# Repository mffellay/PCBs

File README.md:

# PCBs
Personal PCB projects (KiCAD)

**Guitar pedal power supply with 6 isolated outputs**

**USB Audio Interface**
*Ongoing*

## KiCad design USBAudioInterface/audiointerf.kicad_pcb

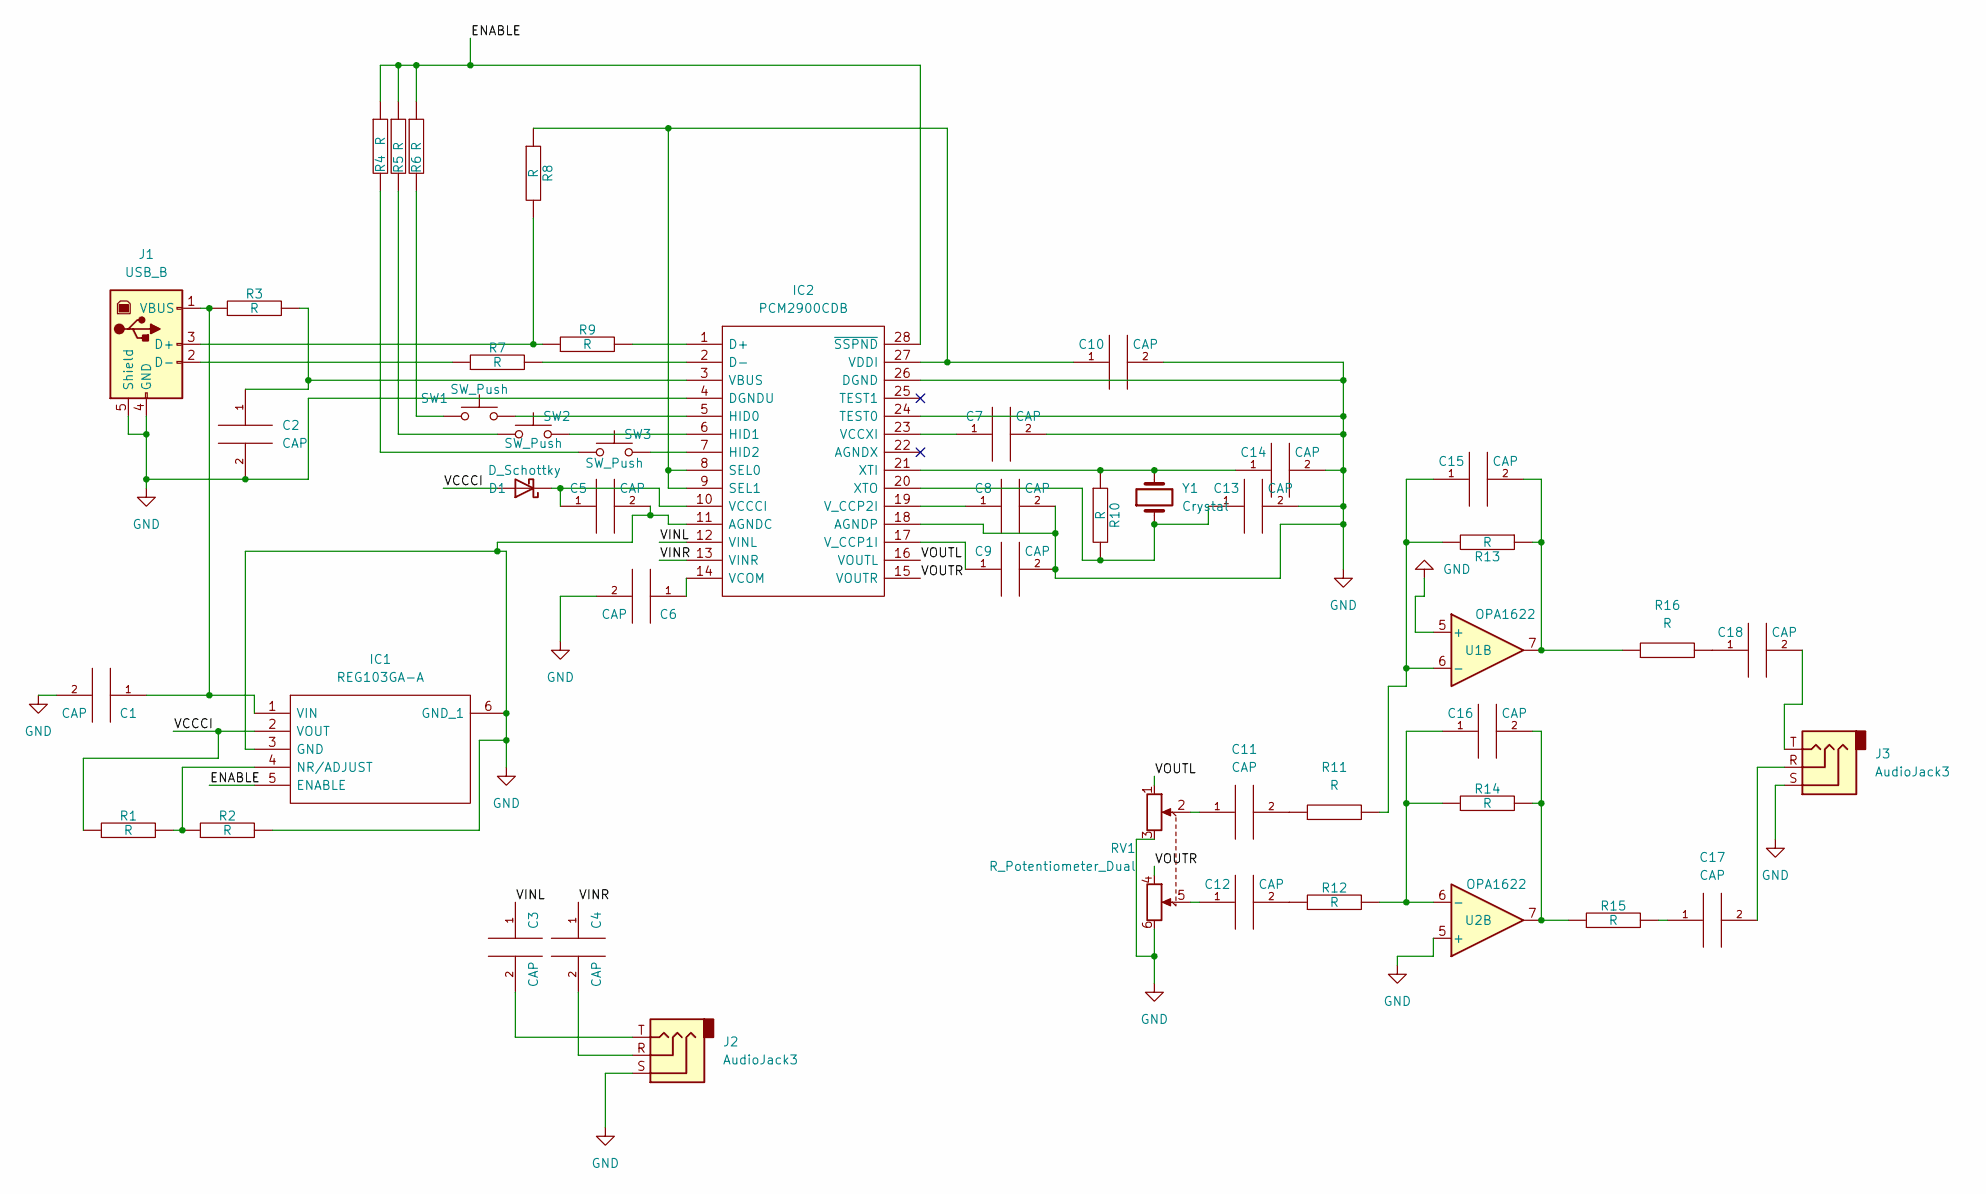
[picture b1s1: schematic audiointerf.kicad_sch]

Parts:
C1, C2, C7, C8, C9, C10, C13, C14, C15, C16, C17, C18: CAP; CP_EIA-2012-15_AVX-P
C3, C4, C5, C6, C11, C12: CAP; CP_Radial_D5.0mm_P2.50mm
D1: D_Schottky; D_2114_3652Metric
IC1: REG103GA-A; SOT-223-6; Manufacturer_Part_Number REG103GA-A; Mouser Part Number 595-REG103GA-A
IC2: PCM2900CDB; SSOP-28_5.3x10.2mm_P0.65mm; Manufacturer_Part_Number PCM2900CDB; Mouser Part Number 595-PCM2900CDB
J1: USB_B; USB_B_Lumberg_2411_02_Horizontal
J2: AudioJack3; Jack_6.35mm_Neutrik_NJ3FD-V_Vertical
J3: AudioJack3; Jack_3.5mm_CUI_SJ-3523-SMT_Horizontal
R1, R2, R3, R4, R5, R6, R7, R8, R9, R10, R11, R12, R13, R14, R15, R16: R; R_0603_1608Metric
RV1: R_Potentiometer_Dual; Potentiometer_Alpha_RD902F-40-00D_Dual_Vertical
SW1, SW2, SW3: SW_Push; SW_CW_GPTS203211B
U1, U2: OPA1622; Texas_S-PVSON-N10
Y1: Crystal; Crystal_DS10_D1.0mm_L4.3mm_Horizontal

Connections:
/ENABLE: IC1.5 (ENABLE), IC2.28 (~SSPND), R4.1, R5.1, R6.1
/VCCCI: D1.2 (A), IC1.2 (VOUT), R1.1
/VINL: C3.1, IC2.12 (VINL)
/VINR: C4.1, IC2.13 (VINR)
/VOUTL: IC2.16 (VOUTL), RV1.1
/VOUTR: IC2.15 (VOUTR), RV1.4
GND: C1.2, C2.2, C5.2, C6.2, C7.2, C8.2, C9.2, C10.2, C13.2, C14.2, IC1.3 (GND), IC1.6 (GND_1), IC2.4 (DGNDU), IC2.11 (AGNDC), IC2.18 (AGNDP), IC2.24 (TEST0), IC2.26 (DGND), J1.4 (GND), J1.5 (Shield), J2.S, J3.S, R2.2, RV1.3, RV1.6, U1.5 (+), U2.5 (+)
unnamed: C1.1, IC1.1 (VIN), J1.1 (VBUS), R3.1
unnamed: C2.1, IC2.3 (VBUS), R3.2
unnamed: C3.2, J2.T
unnamed: C4.2, J2.R
unnamed: C5.1, D1.1 (K), IC2.10 (VCCCI)
unnamed: C6.1, IC2.14 (VCOM)
unnamed: C7.1, IC2.23 (VCCXI)
unnamed: C8.1, IC2.19 (V_CCP2I)
unnamed: C9.1, IC2.17 (V_CCP1I)
unnamed: C10.1, IC2.8 (SEL0), IC2.9 (SEL1), IC2.27 (VDDI), R8.1
unnamed: C11.1, RV1.2
unnamed: C11.2, R11.1
unnamed: C12.1, RV1.5
unnamed: C12.2, R12.1
unnamed: C13.1, IC2.20 (XTO), R10.2, Y1.1
unnamed: C14.1, IC2.21 (XTI), R10.1, Y1.2
unnamed: C16.1, R12.2, R14.1, U2.6 (-)
unnamed: C16.2, R14.2, R15.1, U2.7
unnamed: C17.1, R15.2
unnamed: C17.2, J3.R
unnamed: C18.1, R16.2
unnamed: C18.2, J3.T
unnamed: IC1.4 (NR/ADJUST), R1.2, R2.1
unnamed: IC2.1 (D+), R9.2
unnamed: IC2.2 (D-), R7.2
unnamed: IC2.5 (HID0), SW1.2
unnamed: IC2.6 (HID1), SW2.2
unnamed: IC2.7 (HID2), SW3.2
unnamed: J1.2 (D-), R7.1
unnamed: J1.3 (D+), R8.2, R9.1
unnamed: R4.2, SW3.1
unnamed: R5.2, SW2.1
unnamed: R6.2, SW1.1

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
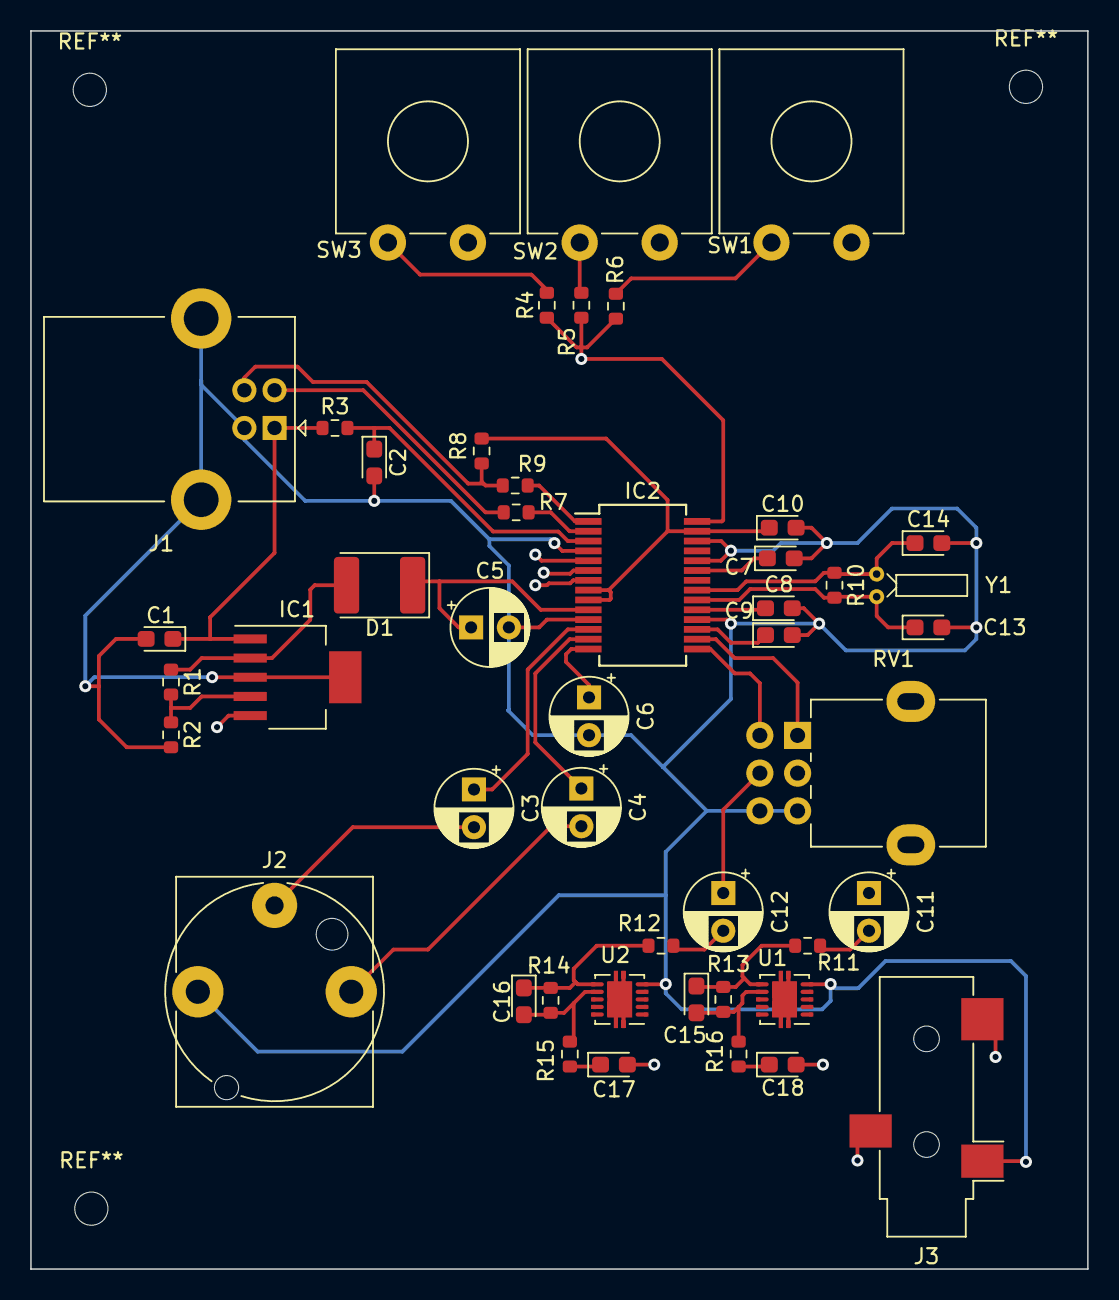
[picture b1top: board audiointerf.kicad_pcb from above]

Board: 4 copper layers, 70.0 x 82.0 mm, 47 parts (0 on the bottom side), 42 nets.

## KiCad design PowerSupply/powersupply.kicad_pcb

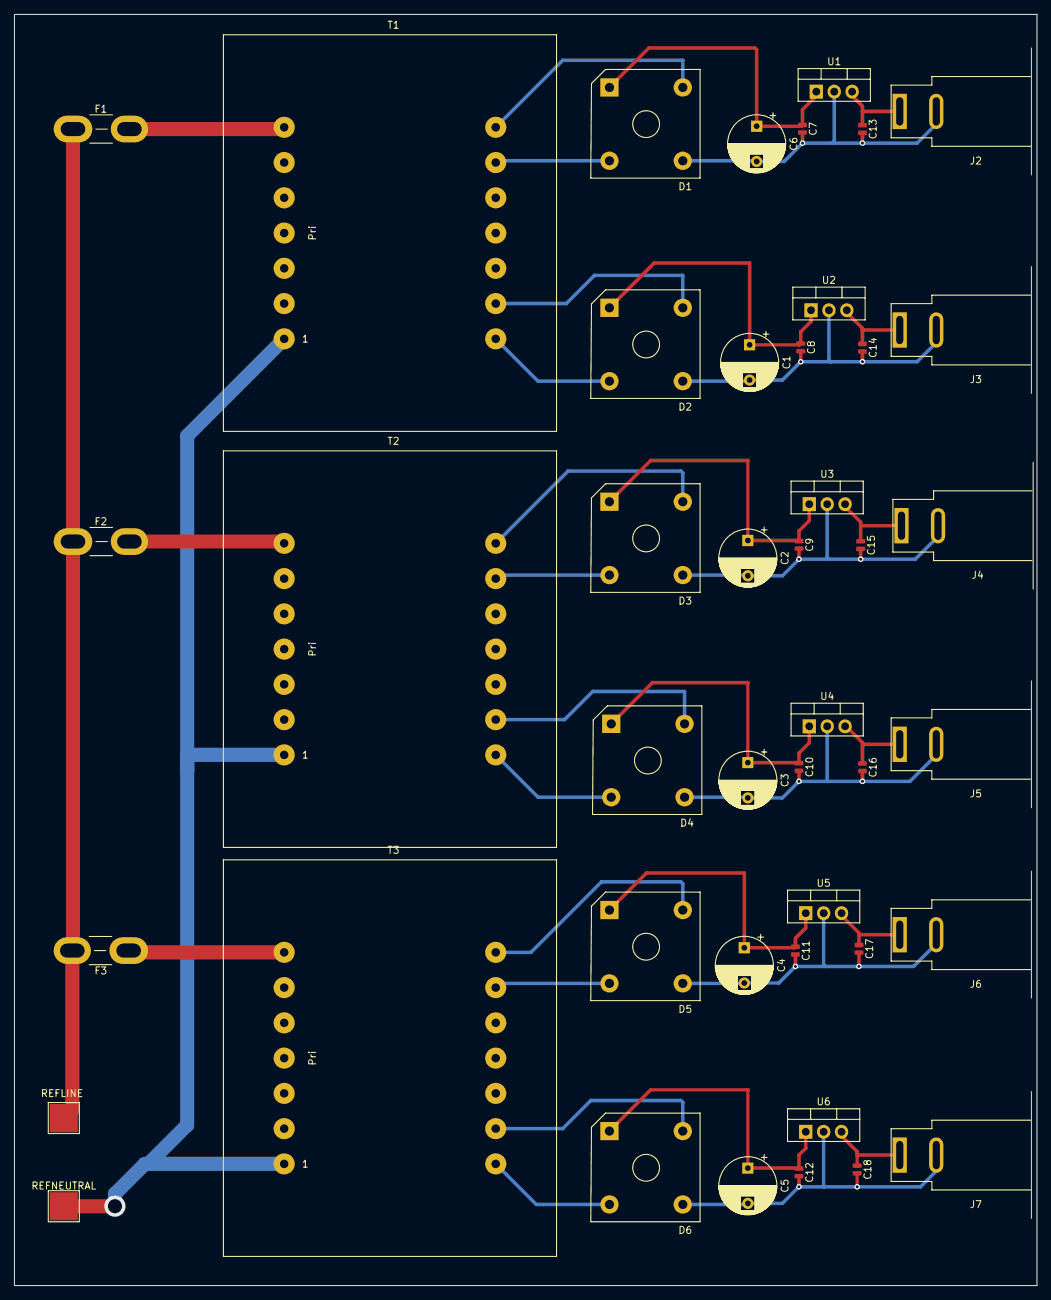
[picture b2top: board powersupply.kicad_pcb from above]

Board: 2 copper layers, 145.0 x 180.2 mm, 44 parts (0 on the bottom side), 30 nets.

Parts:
C1, C2, C3, C4, C5, C6: 470uF; CP_Radial_D8.0mm_P5.00mm
C7, C8, C9, C10, C11, C12: 0.33uF; C_0504_1310Metric
C13, C14, C15, C16, C17, C18: 0.1uF; C_0504_1310Metric
D1, D2, D3, D4, D5, D6: VS-KBPC806; Diode_Bridge_Vishay_KBPC6
F1, F2, F3: Fuse; Fuse_Blade_Mini_directSolder
J2, J3, J4, J5, J6, J7: Jack-DC; BarrelJack_SwitchcraftConxall_RAPC10U_Horizontal
REFLINE: TestPoint_Pad_4.0x4.0mm
REFNEUTRAL: TestPoint_Pad_4.0x4.0mm
T1, T2, T3: Transformer_1P_2S; Transformer_CHK_EI54-12VA_2xSec
U1, U2, U3, U4, U5, U6: L7809; TO-220-3_Vertical

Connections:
GND: C1.2, C2.2, C3.2, C4.2, C5.2, C6.2, C7.2, C8.2, C9.2, C10.2, C11.2, C12.2, C13.2, C14.2, C15.2, C16.2, C17.2, C18.2, D1.3 (-), D2.3 (-), D3.3 (-), D4.3 (-), D5.3 (-), D6.3 (-), J2.2, J3.2, J4.2, J5.2, J6.2, J7.2, U1.2 (GND), U2.2 (GND), U3.2 (GND), U4.2 (GND), U5.2 (GND), U6.2 (GND)
Line: F1.1, F2.1, F3.2, REFLINE.1
unnamed: C1.1, C8.1, D2.1 (+), U2.1 (IN)
unnamed: C2.1, C9.1, D3.1 (+), U3.1 (IN)
unnamed: C6.1, C7.1, D1.1 (+), U1.1 (IN)
unnamed: C3.1, C10.1, D4.1 (+), U4.1 (IN)
unnamed: C4.1, C11.1, D5.1 (+), U5.1 (IN)
unnamed: C5.1, C12.1, D6.1 (+), U6.1 (IN)
unnamed: C13.1, J2.1, U1.3 (OUT)
unnamed: C14.1, J3.1, U2.3 (OUT)
unnamed: C15.1, J4.1, U3.3 (OUT)
unnamed: C16.1, J5.1, U4.3 (OUT)
unnamed: C17.1, J6.1, U5.3 (OUT)
unnamed: C18.1, J7.1, U6.3 (OUT)
unnamed: D1.2, T1.9
unnamed: D1.4, T1.8
unnamed: D2.2, T1.14
unnamed: D2.4, T1.13
unnamed: D3.2, T2.9
unnamed: D3.4, T2.8
unnamed: D4.2, T2.14
unnamed: D4.4, T2.13
unnamed: D5.2, T3.9
unnamed: D5.4, T3.8
unnamed: D6.2, T3.14
unnamed: D6.4, T3.13
unnamed: F1.2, T1.7
unnamed: F2.2, T2.7
unnamed: F3.1, T3.7
Neutral: REFNEUTRAL.1, T1.1 (AA), T2.1 (AA), T3.1 (AA)

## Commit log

2022-10-27 updated files
2022-10-29 updates files
2022-10-31 updated circuit and picture
